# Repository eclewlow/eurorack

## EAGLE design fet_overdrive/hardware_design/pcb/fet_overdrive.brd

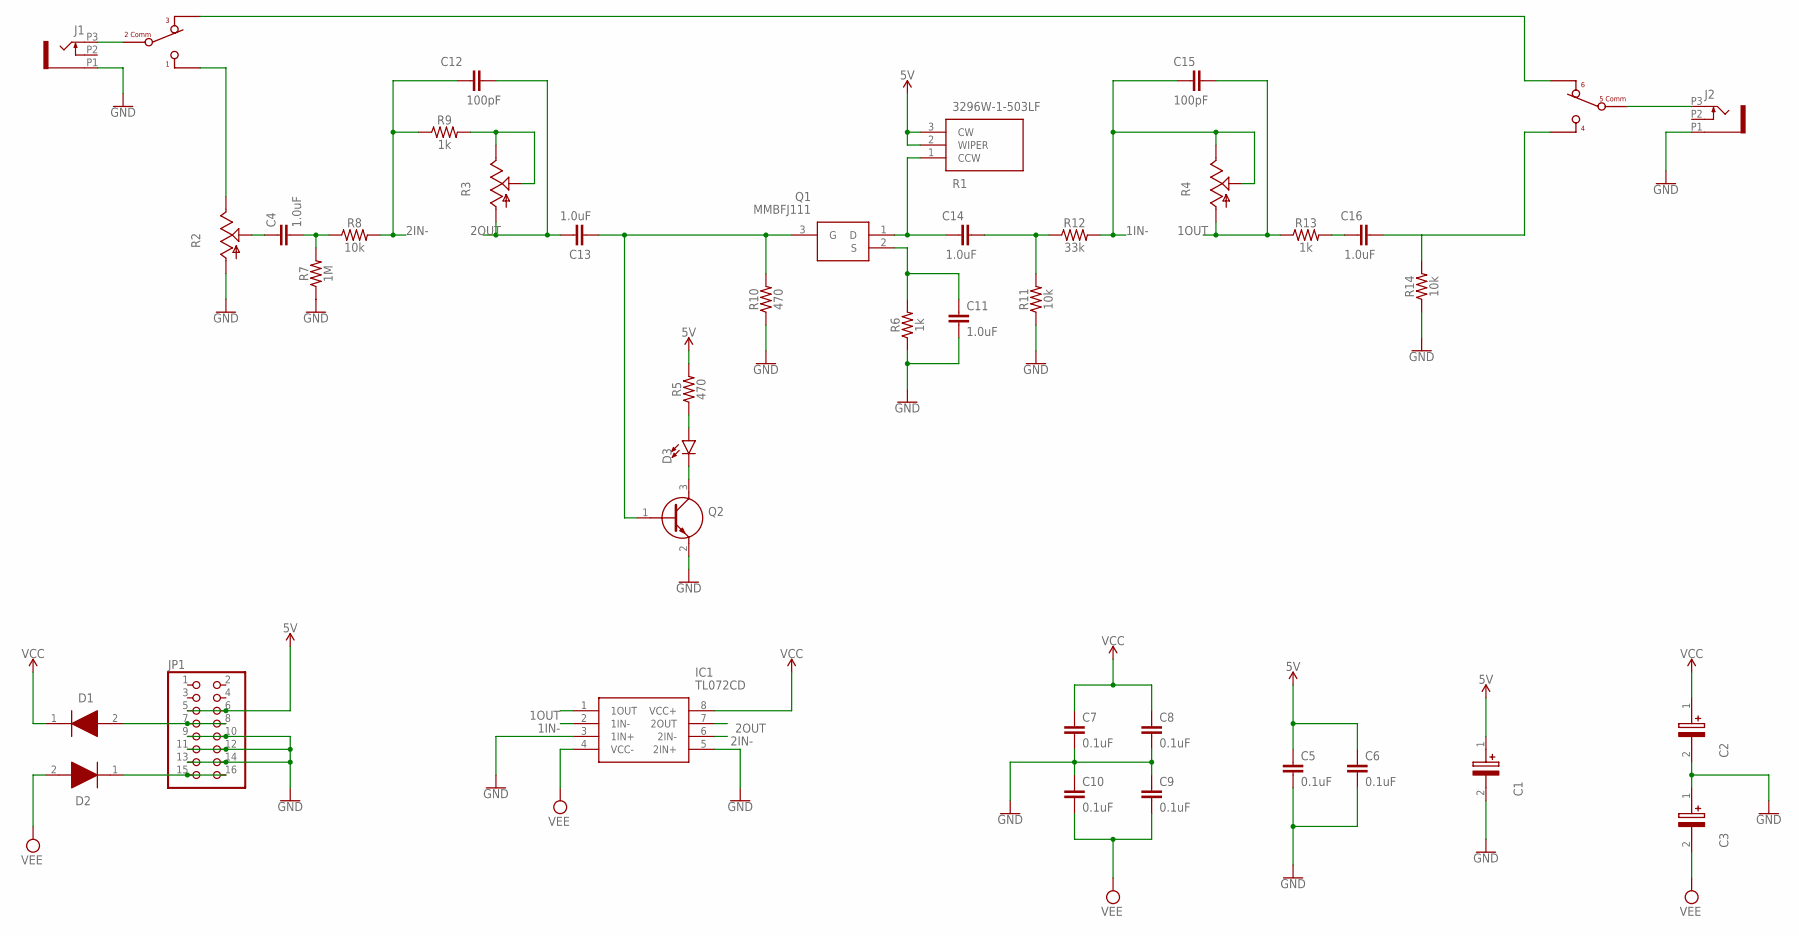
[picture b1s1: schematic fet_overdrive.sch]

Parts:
C1: EEE-FP1E220AR; EEE0GA101SR
C2, C3: EEE-FK1V470P; EEE1AA101SP
C4, C11, C13, C14, C16: 1.0uF; 0603
C5, C6, C7, C8, C9, C10: 0.1uF; 0603
C12, C15: 100pF; 0603
D1, D2: 1N5819HW-7-F; SOD3716X145N
D3: LED3MM; LED_3MM
IC1: TL072CD; SOIC127P600X175-8N
J1, J2: PJ301_THONKICONN6; WQP_PJ_301M6
JP1: PINHD-2X8; 2X08
Q1: MMBFJ111; SOT96P237X111-3N
Q2: SMMBT3904LT1G; SOT96P237X111-3N
R1: 3296W-1-503LF; 3296W-1
R2, R3, R4: POT_USVERTICAL_PS; ALPS_POT_VERTICAL_PS
R5, R10: 470; 0603
R6, R9, R13: 1k; 0603
R7: 1M; 0603
R8, R11, R14: 10k; 0603
R12: 33k; 0603
U$1: DAILYWELL-DPDT

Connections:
1IN-: C15.1, IC1.2 (1IN-), R4.P$1 (E), R4.P$2 (S), R12.2
1OUT: C15.2, IC1.1 (1OUT), R4.P$3 (A), R13.1
2IN-: C12.1, IC1.6 (2IN-), R8.2, R9.1
2OUT: C12.2, C13.1, IC1.7 (2OUT), R3.P$3 (A)
5V: C1.1 (+), C5.1, C6.1, JP1.5, JP1.6, R1.2 (WIPER), R1.3 (CW), R5.2
GND: C1.2 (-), C2.2 (-), C3.1 (+), C5.2, C6.2, C7.2, C8.2, C9.1, C10.1, C11.2, IC1.3 (1IN+), IC1.5 (2IN+), J1.P1 (1), J2.P1 (1), JP1.9, JP1.10, JP1.11, JP1.12, JP1.13, JP1.14, Q2.2 (E), R2.P$3 (A), R6.1, R7.1, R10.1, R11.1, R14.1
unnamed: C16.2, R14.2, U$1.P$4
unnamed: J1.P3 (3), U$1.P$2
unnamed: D1.2 (A), JP1.7, JP1.8
unnamed: C4.1, R2.P$2 (S)
unnamed: C14.1, Q1.1 (D), R1.1 (CCW)
unnamed: R2.P$1 (E), U$1.P$1
unnamed: D3.A, R5.1
unnamed: D3.K (C), Q2.3 (C)
unnamed: C4.2, R7.2, R8.1
unnamed: D2.1 (K), JP1.15, JP1.16
unnamed: C14.2, R11.2, R12.1
unnamed: C13.2, Q1.3 (G), Q2.1 (B), R10.2
unnamed: C11.1, Q1.2 (S), R6.2
unnamed: R3.P$1 (E), R3.P$2 (S), R9.2
unnamed: U$1.P$3, U$1.P$6
unnamed: C16.1, R13.2
unnamed: J2.P3 (3), U$1.P$5
VCC: C2.1 (+), C7.1, C8.1, D1.1 (K), IC1.8 (VCC+)
VEE: C3.2 (-), C9.2, C10.2, D2.2 (A), IC1.4 (VCC-)

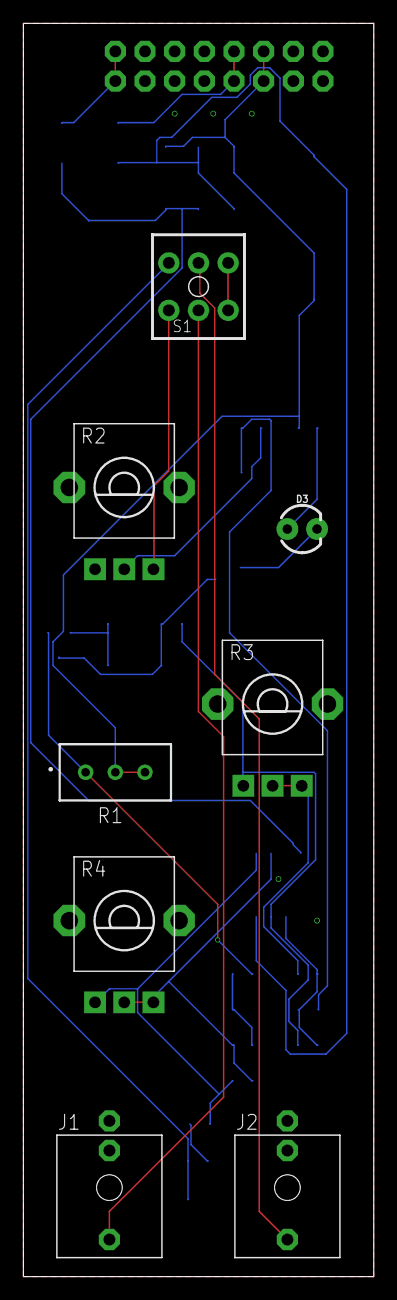
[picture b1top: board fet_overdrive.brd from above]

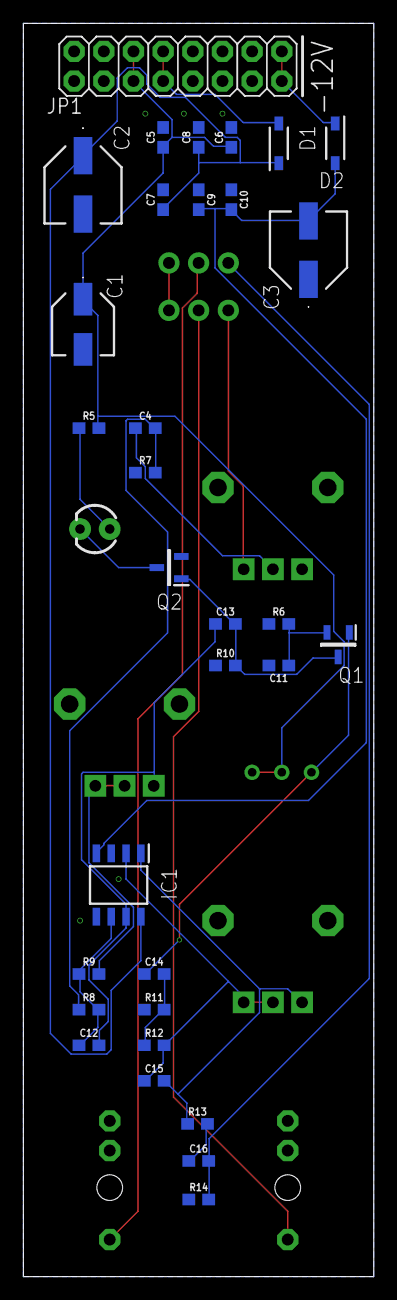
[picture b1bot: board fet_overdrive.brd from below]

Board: 2 copper layers, 30.0 x 107.3 mm, 40 parts (32 on the bottom side), 25 nets.

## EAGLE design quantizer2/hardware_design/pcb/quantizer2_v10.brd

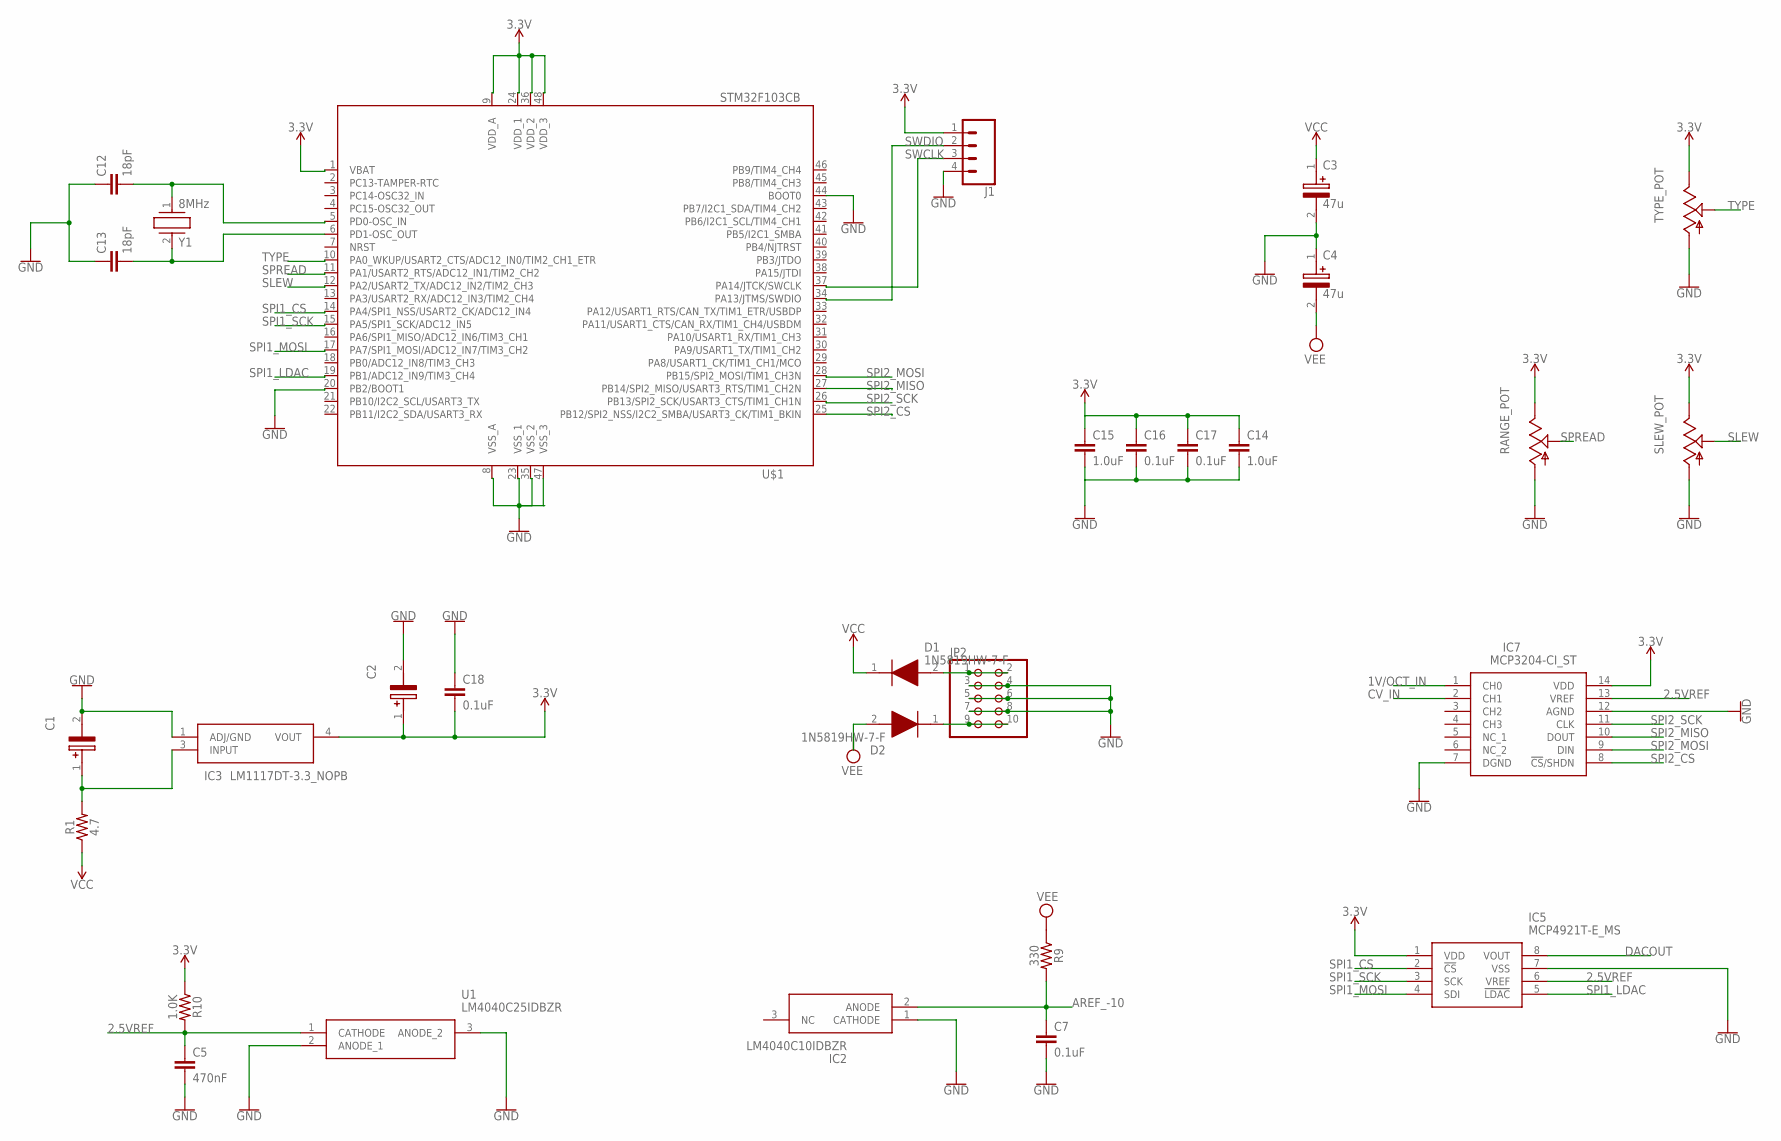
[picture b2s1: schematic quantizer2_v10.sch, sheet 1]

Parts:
C1, C2: 22uF; EEE0GA101SR
C3, C4: 47u; EEE1AA101SP
C5: 470nF; 0603
C7, C16, C17, C18: 0.1uF; 0603
C12, C13: 18pF; 0603
C14, C15: 1.0uF; 0603
D1, D2: 1N5819HW-7-F; SOD3716X145N
IC2: LM4040C10IDBZR; SOT95P237X112-3N
IC3: LM1117DT-3.3_NOPB; TO228P991X238-3N
IC5: MCP4921T-E_MS; SOP65P490X110-8N
IC7: MCP3204-CI_ST; SOP65P640X120-14N
J1: CONN_04; 1X04
JP2: PINHD-2X5; 2X05
R1: 4.7; 1206
R9: 330; 0603
R10: 1.0K; 0603
RANGE_POT: POT_USVERTICAL_PS; ALPS_POT_VERTICAL_PS
SLEW_POT: POTENTIOMETER-ALPHA-9MM_VERTICAL_; POTENTIOMETER-ALPHA-9MM_VERTICAL
TYPE_POT: POT_USVERTICAL_PS; ALPS_POT_VERTICAL_PS
U1: LM4040C25IDBZR; SOT95P237X112-3N
U$1: STM32F103CB; LQFP48
Y1: 8MHz; ABLS

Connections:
1V/OCT_IN: IC7.1 (CH0); also elsewhere on the board
2.5VREF: C5.1, IC5.6 (VREF), IC7.13 (VREF), R10.2, U1.1 (CATHODE)
3.3V: C2.1 (+), C18.2, IC3.4 (VOUT), IC5.1 (VDD), IC7.14 (VDD), J1.1, R10.1, RANGE_POT.P$1 (E), SLEW_POT.3 (E), TYPE_POT.P$1 (E), U$1.1 (VBAT), U$1.9 (VDD_A), U$1.24 (VDD_1), U$1.36 (VDD_2), U$1.48 (VDD_3)
AREF_-10: C7.1, IC2.2 (ANODE), R9.2; also elsewhere on the board
CV_IN: IC7.2 (CH1)
DACOUT: IC5.8 (VOUT); also elsewhere on the board
GND: C1.2 (-), C2.2 (-), C3.2 (-), C4.1 (+), C5.2, C7.2, C12.1, C13.1, C18.1, IC2.1 (CATHODE), IC3.1 (ADJ/GND), IC5.7 (VSS), IC7.7 (DGND), IC7.12 (AGND), J1.4, JP2.3, JP2.4, JP2.5, JP2.6, JP2.7, JP2.8, RANGE_POT.P$3 (A), SLEW_POT.1 (A), TYPE_POT.P$3 (A), U1.2 (ANODE_1), U1.3 (ANODE_2), U$1.8 (VSS_A), U$1.20 (PB2/BOOT1), U$1.23 (VSS_1), U$1.35 (VSS_2), U$1.44 (BOOT0), U$1.47 (VSS_3); also elsewhere on the board
unnamed: C1.1 (+), IC3.3 (INPUT), R1.2
unnamed: D1.2 (A), JP2.1, JP2.2
unnamed: D2.1 (K), JP2.9, JP2.10
unnamed: C12.2, U$1.5 (PD0-OSC_IN), Y1.1
unnamed: C13.2, U$1.6 (PD1-OSC_OUT), Y1.2
unnamed: C14.1, C15.1, C16.1, C17.1
unnamed: C14.2, C15.2, C16.2, C17.2
SLEW: SLEW_POT.2 (S), U$1.12 (PA2/USART2_TX/ADC12_IN2/TIM2_CH3)
SPI1_CS: IC5.2 (!CS), U$1.14 (PA4/SPI1_NSS/USART2_CK/ADC12_IN4)
SPI1_LDAC: IC5.5 (!LDAC), U$1.19 (PB1/ADC12_IN9/TIM3_CH4)
SPI1_MOSI: IC5.4 (SDI), U$1.17 (PA7/SPI1_MOSI/ADC12_IN7/TIM3_CH2)
SPI1_SCK: IC5.3 (SCK), U$1.15 (PA5/SPI1_SCK/ADC12_IN5)
SPI2_CS: IC7.8 (!CS!/SHDN), U$1.25 (PB12/SPI2_NSS/I2C2_SMBA/USART3_CK/TIM1_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)
SPI2_MISO: IC7.10 (DOUT), U$1.27 (PB14/SPI2_MISO/USART3_RTS/TIM1_CH2N)
SPI2_MOSI: IC7.9 (DIN), U$1.28 (PB15/SPI2_MOSI/TIM1_CH3N)
SPI2_SCK: IC7.11 (CLK), U$1.26 (PB13/SPI2_SCK/USART3_CTS/TIM1_CH1N)
SPREAD: RANGE_POT.P$2 (S), U$1.11 (PA1/USART2_RTS/ADC12_IN1/TIM2_CH2)
SWCLK: J1.3, U$1.37 (PA14/JTCK/SWCLK)
SWDIO: J1.2, U$1.34 (PA13/JTMS/SWDIO)
TYPE: TYPE_POT.P$2 (S), U$1.10 (PA0_WKUP/USART2_CTS/ADC12_IN0/TIM2_CH1_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)
VCC: C3.1 (+), D1.1 (K), R1.1; also elsewhere on the board
VEE: C4.2 (-), D2.2 (A), R9.1; also elsewhere on the board

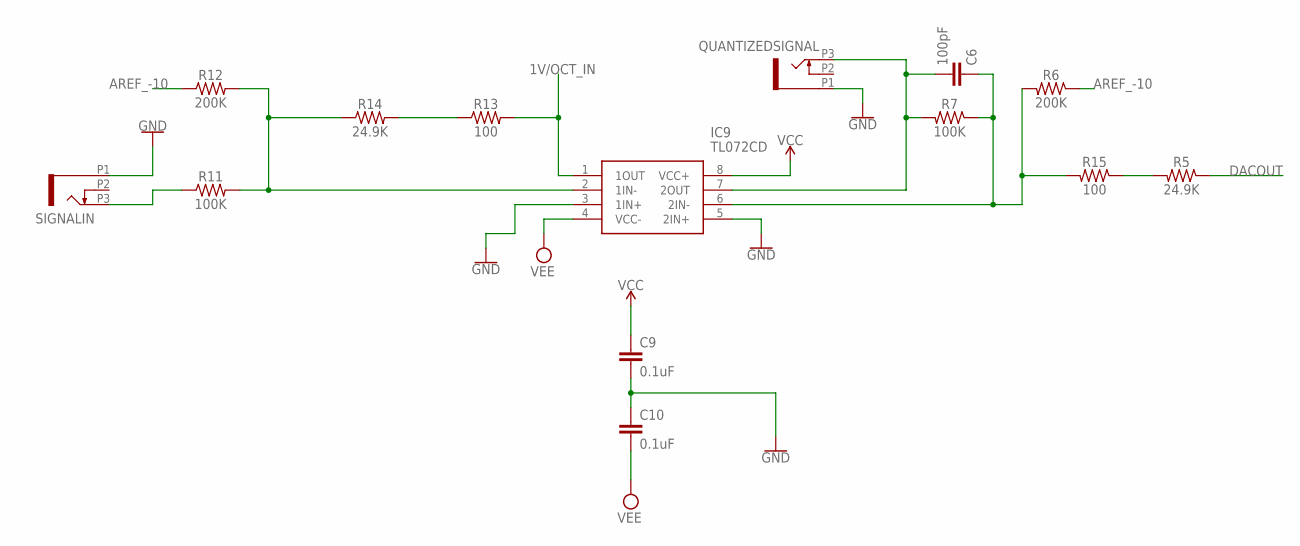
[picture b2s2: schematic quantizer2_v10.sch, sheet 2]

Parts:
C6: 100pF; 0603
C9, C10: 0.1uF; 0603
IC9: TL072CD; SOIC127P600X175-8N
QUANTIZEDSIGNAL: PJ301_THONKICONN6; WQP_PJ_301M6
R5, R14: 24.9K; 0603
R6, R12: 200K; 0603
R7, R11: 100K; 0603
R13, R15: 100; 0603
SIGNALIN: PJ301_THONKICONN6; WQP_PJ_301M6

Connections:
1V/OCT_IN: IC9.1 (1OUT), R13.2; also elsewhere on the board
AREF_-10: R6.1, R12.1; also elsewhere on the board
DACOUT: R5.1; also elsewhere on the board
GND: C9.2, C10.1, IC9.3 (1IN+), IC9.5 (2IN+), QUANTIZEDSIGNAL.P1 (1), SIGNALIN.P1 (1); also elsewhere on the board
unnamed: R11.1, SIGNALIN.P3 (3)
unnamed: IC9.2 (1IN-), R11.2, R12.2, R14.1
unnamed: C6.2, IC9.7 (2OUT), QUANTIZEDSIGNAL.P3 (3), R7.2
unnamed: R13.1, R14.2
unnamed: R5.2, R15.1
unnamed: C6.1, IC9.6 (2IN-), R6.2, R7.1, R15.2
VCC: C9.1, IC9.8 (VCC+); also elsewhere on the board
VEE: C10.2, IC9.4 (VCC-); also elsewhere on the board

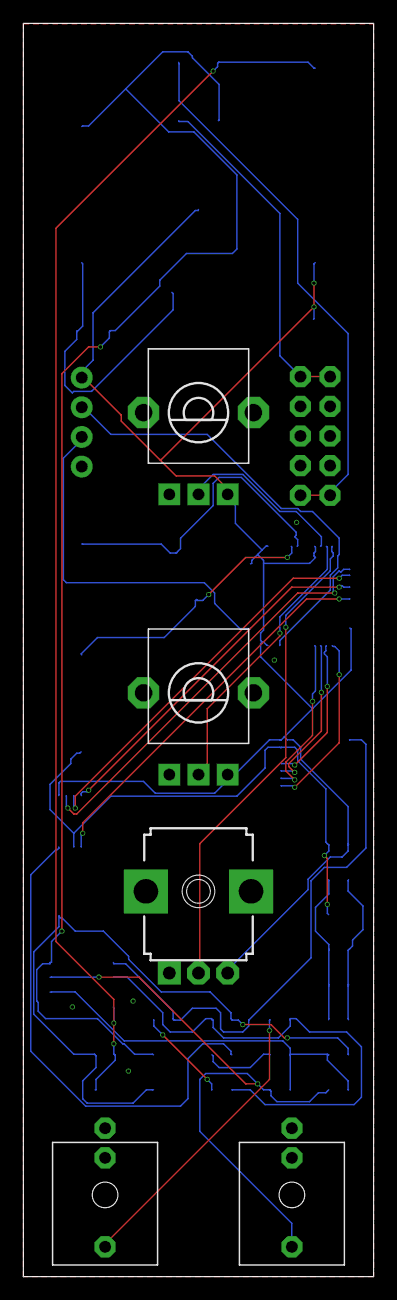
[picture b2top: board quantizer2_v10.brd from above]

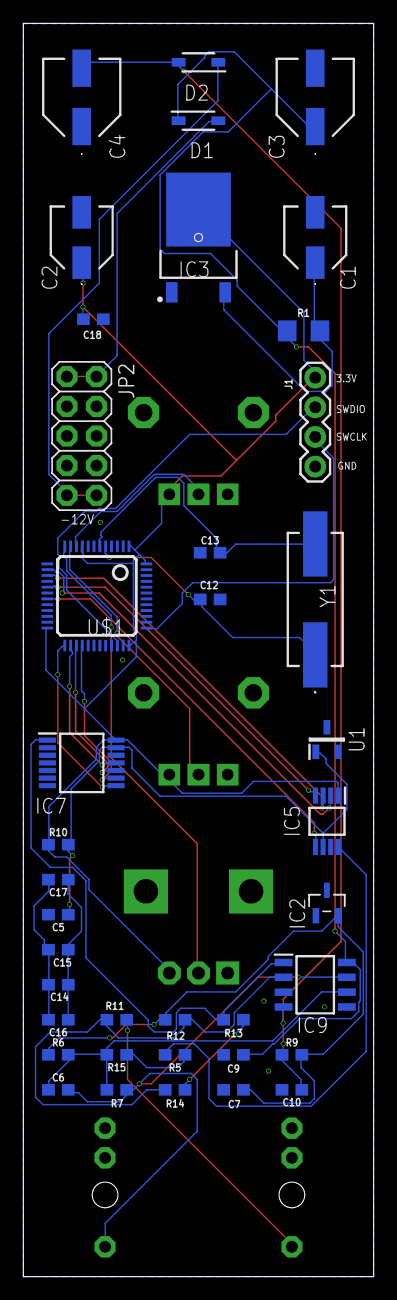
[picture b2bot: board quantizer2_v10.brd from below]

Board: 2 copper layers, 30.0 x 107.3 mm, 44 parts (39 on the bottom side), 34 nets.

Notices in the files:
parts and their libraries:
SparkFun-Capacitors: Licensing: Creative Commons ShareAlike 4.0 International - https://creativecommons.org/licenses/by-sa/4.0
